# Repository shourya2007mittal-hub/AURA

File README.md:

# AURA

I made a custom Tailless twin motor RC Plane with custom Flight Controller (based on STM32). The Flight Controller  will have 2 IMU's and a barometer for precise data collection. The Plane design will include a tailless structure and the motions will be controlled by the flaps on the wings. I have also made custom ESc for the Plane as well.

## Features
- Base on  STM32F401CBUx 
- Has dual IMU (MPU_6050)(ICM-20948)
- Has a Barometer (BMP280)
- Uses 2 Light-Weight Servoes
- Uses Custom flight-controller
- Tailless twin motor Design
- Custom ESC for plane 

# ✈️ RC Plane Bill of Materials (BOM)

This repository contains the complete **Bill of Materials (BOM)** for the RC Plane project, including component quantities, unit prices, total costs, and supplier links.

## 📦 Bill of Materials

| Item | Quantity | Unit Price (USD) | Total Price (USD) | Source |
|------|:--------:|-----------------:|------------------:|--------|
| PCB + PCBA (Flight Controller + ESC) | 1 | $253.46 | $253.46 | https://jlcpcb.com |
| PCB Shipping + coupons | 1 | $17.32 | $17.32 | https://jlcpcb.com |
| Brushless Motor | 2 | $15.20 | $30.40 | https://robu.in/product/r2207-2207-2450kv-ccw-fpv-brushless-motor/ |
| Receiver / Transmitter | 1 | $0 | $0 Funded by me |https://robocraze.com/products/fly-sky-fs-i6x-2-4ghz-6ch-afhds-2a-rc-transmitter-with-fs-ia10b-2-4ghz-10ch-receiver?_pos=6&_sid=c7af4b55f&_ss=r |
| 12V Battery | 1 | $5.78 | $5.78 | https://robocraze.com/products/11-1v-2200mah-li-ion-battery?_pos=18&_sid=25292ddd5&_ss=r |
| SG90 Servo | 2 | $0.96 | $1.92 | https://robocraze.com/products/sg90-micro-servo-motor?_pos=1&_sid=88e48e080&_ss=r |
| 3D Printed Plane | 1 | $41.86 | $41.86 |https://jlc3dp.com/ |

---

## 💰 Cost Summary

| Category | Amount (USD) |
|----------|-------------:|
| Total Component Cost | **$352.74** |

---

## 📋 Components Included

- PCB + PCBA
- PCB Shipping
- Brushless Motors (×2)
- Electronic Speed Controllers (ESCs) (×2)
- Receiver / Transmitter
- 12V Battery
- SG90 Micro Servos (×2)
- 3D Printed Aircraft Frame

### Schematic Flight Controller

###  PCB Design Flight Controller

### Schematic ESC

###  PCB Design ESC

### 3D Design

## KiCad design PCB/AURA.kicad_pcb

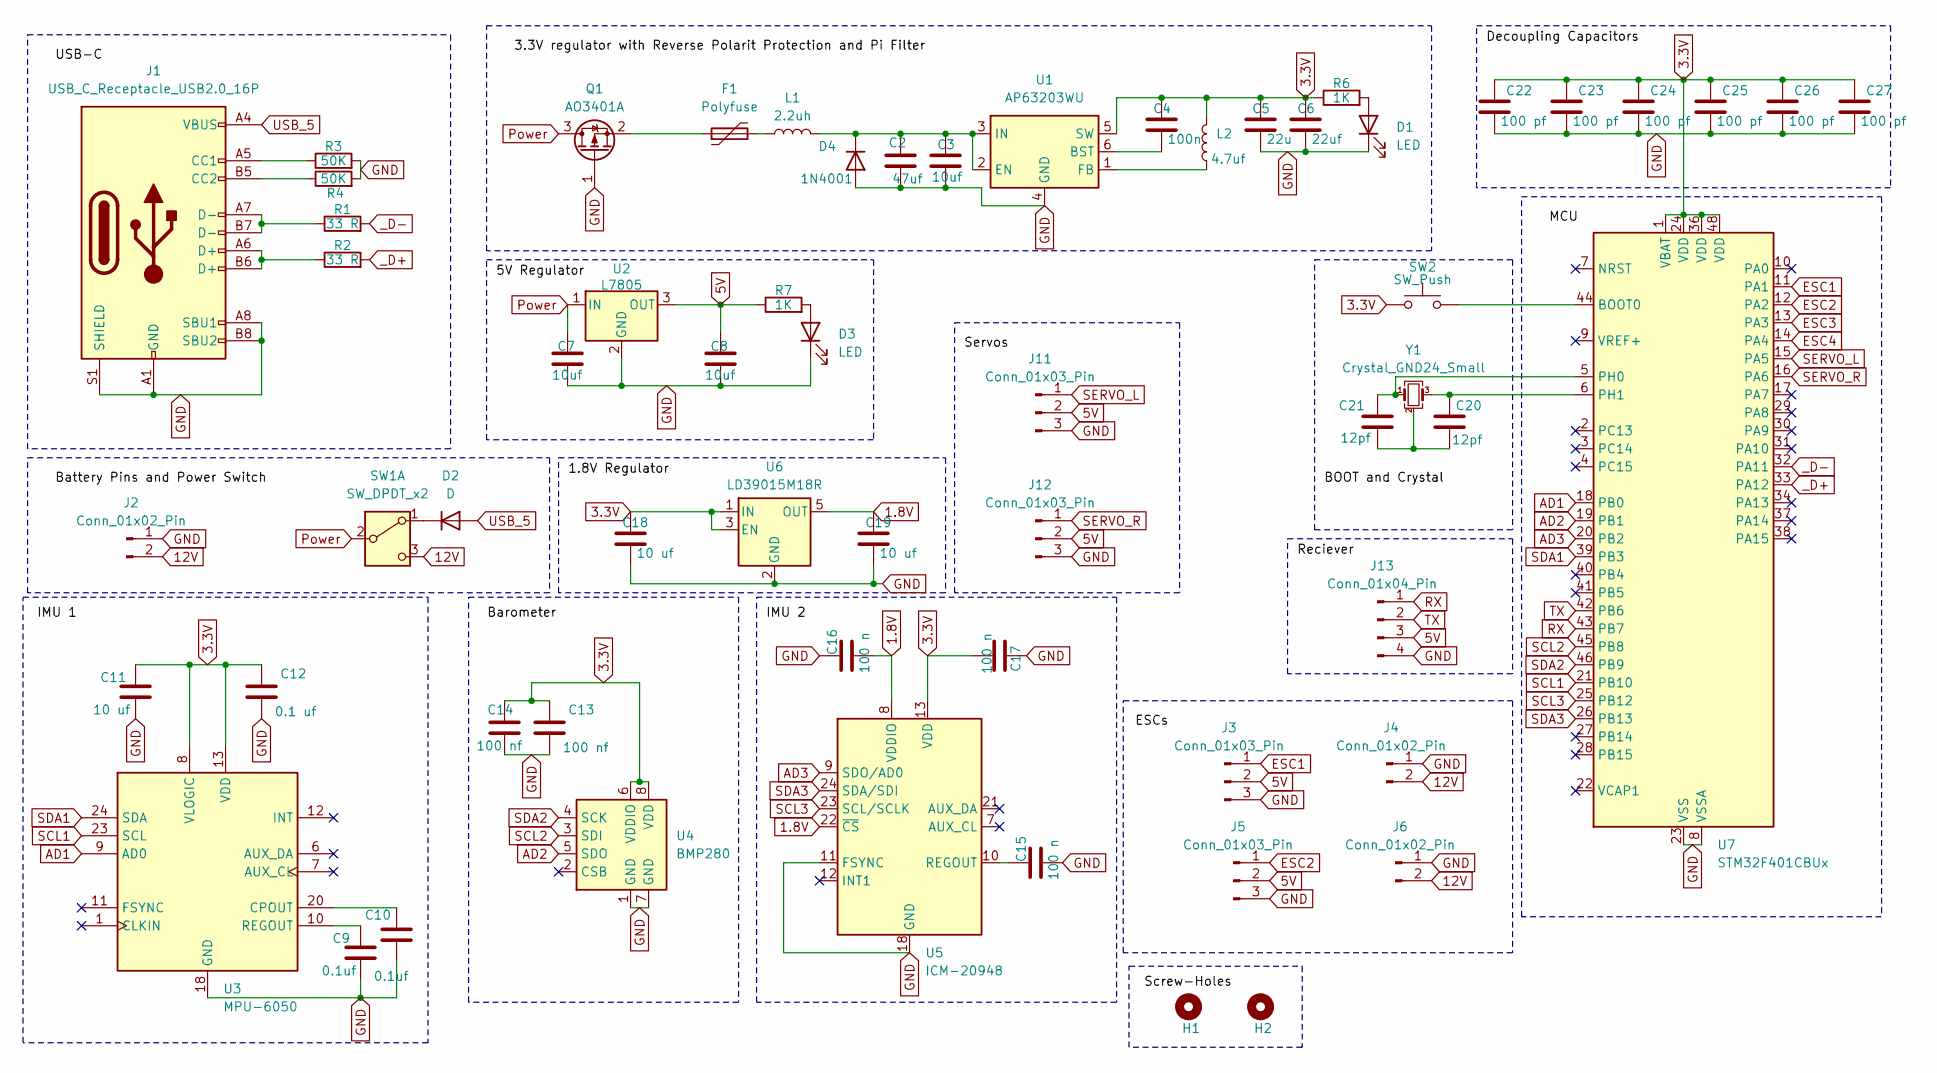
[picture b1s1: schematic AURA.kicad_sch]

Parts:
C2: 47uf; C_0201_0603Metric
C3, C7, C8: 10uf; C_0201_0603Metric
C4: 100n; C_0201_0603Metric
C5: 22u; C_0201_0603Metric
C6: 22uf; C_0201_0603Metric
C9, C10: 0.1uf; C_0201_0603Metric
C11, C18, C19: 10 uf; C_0201_0603Metric
C12: 0.1 uf; C_0201_0603Metric
C13, C14: 100 nf; C_0201_0603Metric
C15, C16, C17: 100 n; C_0201_0603Metric
C20, C21: 12pf; C_0201_0603Metric
C22, C23, C24, C25, C26, C27: 100 pf; C_0201_0603Metric
D1, D3: LED; LED_0201_0603Metric
D2: D; D_0201_0603Metric
D4: 1N4001; D_DO-41_SOD81_P5.08mm_Vertical_AnodeUp
F1: Polyfuse; C_0201_0603Metric
H1, H2: MountingHole; MountingHole_2.5mm_Pad
J1: USB_C_Receptacle_USB2.0_16P; USB_C_Receptacle_G-Switch_GT-USB-7010ASV
J2: Conn_01x02_Pin; AMASS_XT60-M_1x02_P7.20mm_Vertical
J3, J5, J11, J12: Conn_01x03_Pin; JST_EH_B3B-EH-A_1x03_P2.50mm_Vertical
J4, J6: Conn_01x02_Pin; AMASS_XT60-F_1x02_P7.20mm_Vertical
J13: Conn_01x04_Pin; JST_EH_B4B-EH-A_1x04_P2.50mm_Vertical
L1: 2.2uh; L_0603_1608Metric
L2: 4.7uf; L_0603_1608Metric
Q1: AO3401A; SOT-23
R1, R2: 33 R; R_0201_0603Metric_Pad0.64x0.40mm_HandSolder
R3, R4: 50K; R_0201_0603Metric_Pad0.64x0.40mm_HandSolder
R6, R7: 1K; R_0201_0603Metric_Pad0.64x0.40mm_HandSolder
SW1: SW_DPDT_x2; SW_PUSH_E-Switch_FS5700DP_DPDT
SW2: SW_Push; SW_Tactile_Straight_KSA0Axx1LFTR
U1: AP63203WU; TSOT-23-6
U2: L7805; TO-252-2
U3: MPU-6050; InvenSense_QFN-24_4x4mm_P0.5mm
U4: BMP280; Bosch_LGA-8_2x2.5mm_P0.65mm_ClockwisePinNumbering
U5: ICM-20948; InvenSense_QFN-24_3x3mm_P0.4mm
U6: LD39015M18R; SOT-23-5
U7: STM32F401CBUx; QFN-48-1EP_7x7mm_P0.5mm_EP5.6x5.6mm
Y1: Crystal_GND24_Small; Crystal_SMD_0603-4Pin_6.0x3.5mm

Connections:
1.8V: C16.2, C19.1, U5.8 (VDDIO), U5.22 (~CS), U6.5 (OUT)
3.3V: C4.1, C5.1, C6.1, C11.1, C12.1, C13.1, C14.1, C17.2, C18.1, C22.1, C23.1, C24.1, C25.1, C26.1, C27.1, L2.2, R6.1, SW2.1, U1.5 (SW), U3.8 (VLOGIC), U3.13 (VDD), U4.6 (VDDIO), U4.8 (VDD), U5.13 (VDD), U6.1 (IN), U6.3 (EN), U7.1 (VBAT), U7.24 (VDD), U7.36 (VDD), U7.48 (VDD)
5V: C8.1, J3.2, J5.2, J11.2, J12.2, J13.3, R7.1, U2.3 (OUT)
12V: J2.2, J4.2, J6.2, SW1.3 (C)
AD1: U3.9 (AD0), U7.18 (PB0)
AD2: U4.5 (SDO), U7.19 (PB1)
AD3: U5.9 (SDO/AD0), U7.20 (PB2)
ESC1: J3.1, U7.11 (PA1)
ESC2: J5.1, U7.12 (PA2)
ESC3: U7.13 (PA3)
ESC4: U7.14 (PA4)
GND: C2.2, C3.2, C5.2, C6.2, C7.2, C8.2, C9.2, C10.2, C11.2, C12.2, C13.2, C14.2, C15.2, C16.1, C17.1, C18.2, C19.2, C22.2, C23.2, C24.2, C25.2, C26.2, C27.2, D1.1 (K), D3.1 (K), D4.2 (A), J1.A1 (GND), J1.A8 (SBU1), J1.A12 (GND), J1.B1 (GND), J1.B8 (SBU2), J1.B12 (GND), J1.S1 (SHIELD), J2.1, J3.3, J4.1, J5.3, J6.1, J11.3, J12.3, J13.4, Q1.1 (G), R3.2, R4.2, U1.4 (GND), U2.2 (GND), U3.18 (GND), U4.1 (GND), U4.7 (GND), U5.11 (FSYNC), U5.18 (GND), U5.20 (GND), U6.2 (GND), U7.8 (VSSA), U7.23 (VSS), U7.35 (VSS), U7.47 (VSS), U7.49 (VSS)
unnamed: C20.2, C21.2, Y1.2 (G), Y1.4 (G)
unnamed: D1.2 (A), R6.2
unnamed: D2.1 (K), SW1.1 (A)
unnamed: D3.2 (A), R7.2
unnamed: C2.1, C3.1, D4.1 (K), L1.2, U1.2 (EN), U1.3 (IN)
unnamed: F1.2, L1.1
unnamed: J1.A5 (CC1), R3.1
unnamed: J1.B5 (CC2), R4.1
unnamed: J1.A6 (D+), J1.B6 (D+), R2.1
unnamed: J1.A7 (D-), J1.B7 (D-), R1.1
unnamed: F1.1, Q1.2 (S)
unnamed: C4.2, U1.6 (BST)
unnamed: L2.1, U1.1 (FB)
unnamed: C10.1, U3.20 (CPOUT)
unnamed: C9.1, U3.10 (REGOUT)
unnamed: C15.1, U5.10 (REGOUT)
unnamed: SW2.2, U7.44 (BOOT0)
unnamed: C21.1, U7.5 (PH0), Y1.1
unnamed: C20.1, U7.6 (PH1), Y1.3
Power: C7.1, Q1.3 (D), SW1.2 (B), U2.1 (IN)
RX: J13.1, U7.43 (PB7)
SCL1: U3.23 (SCL), U7.21 (PB10)
SCL2: U4.3 (SDI), U7.45 (PB8)
SCL3: U5.23 (SCL/SCLK), U7.25 (PB12)
SDA1: U3.24 (SDA), U7.39 (PB3)
SDA2: U4.4 (SCK), U7.46 (PB9)
SDA3: U5.24 (SDA/SDI), U7.26 (PB13)
SERVO_L: J11.1, U7.15 (PA5)
SERVO_R: J12.1, U7.16 (PA6)
TX: J13.2, U7.42 (PB6)
USB_5: D2.2 (A), J1.A4 (VBUS), J1.A9 (VBUS), J1.B4 (VBUS), J1.B9 (VBUS)
_D+: R2.2, U7.33 (PA12)
_D-: R1.2, U7.32 (PA11)

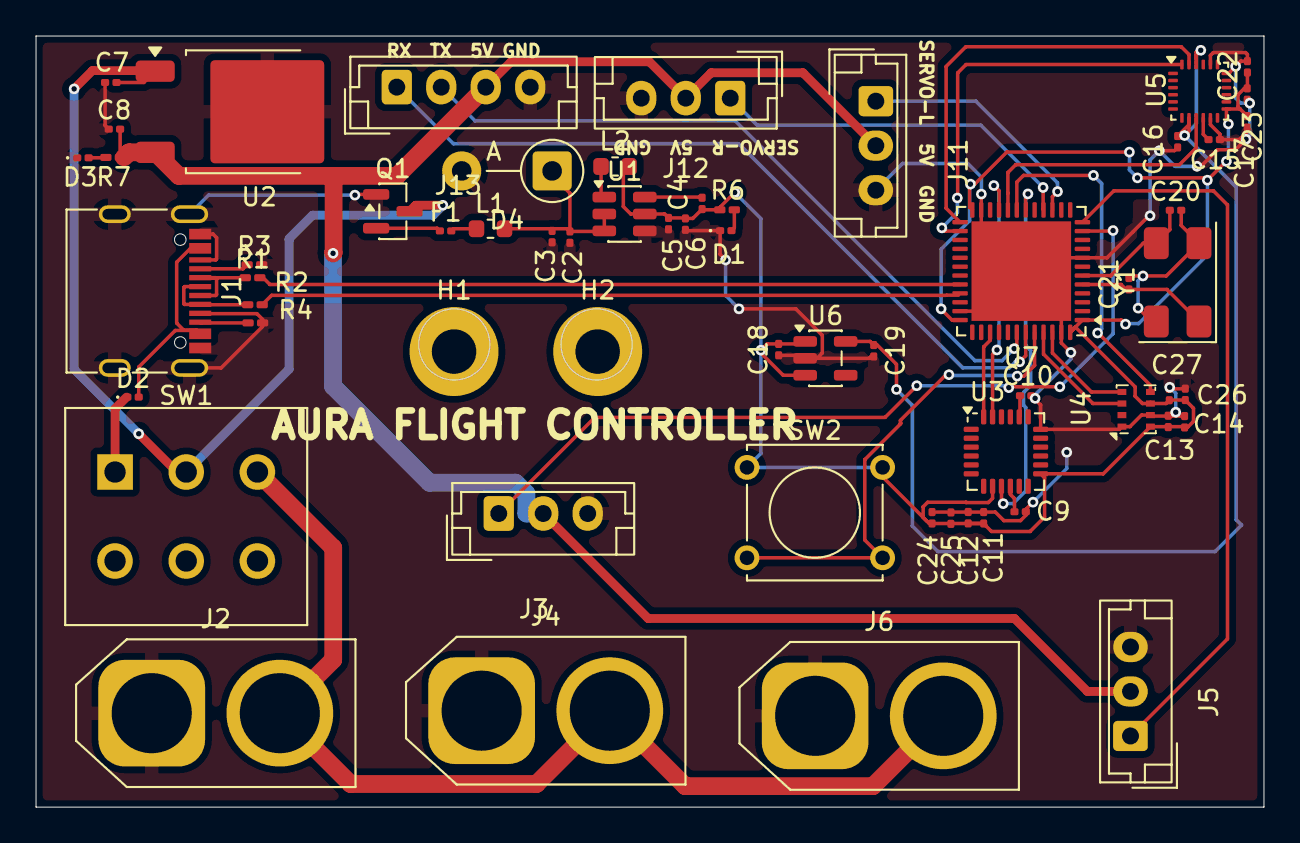
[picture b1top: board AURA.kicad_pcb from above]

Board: 2 copper layers, 69.0 x 43.3 mm, 61 parts (0 on the bottom side), 43 nets.

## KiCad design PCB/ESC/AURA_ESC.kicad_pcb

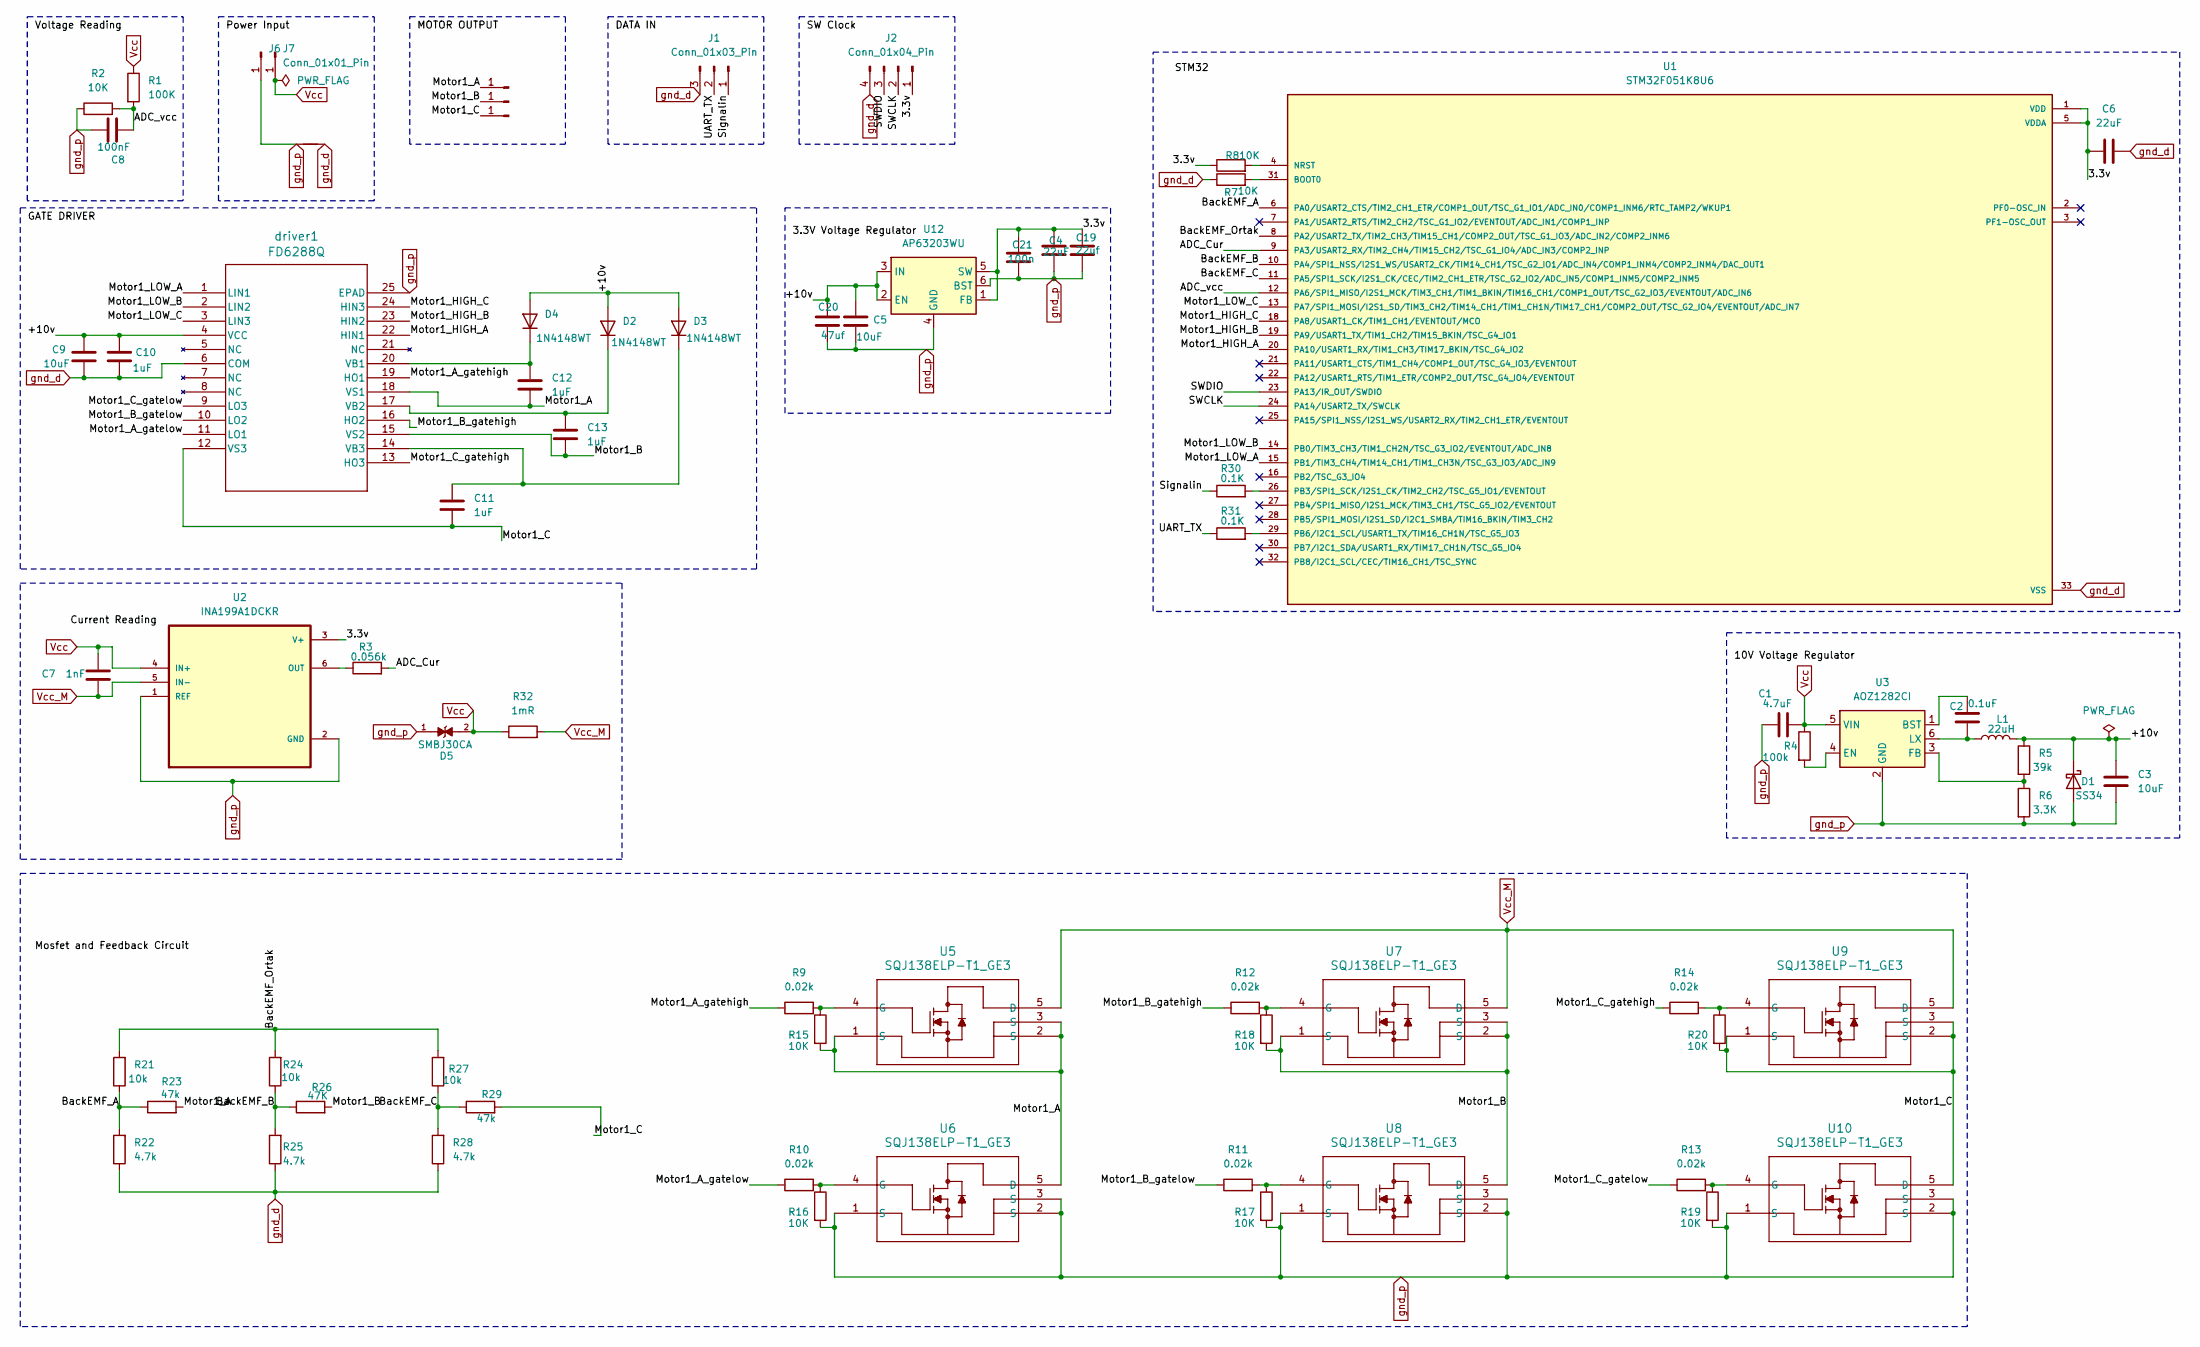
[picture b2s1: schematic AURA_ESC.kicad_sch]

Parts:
C1: 4.7uF; C_0805_2012Metric
C2: 0.1uF; C_0603_1608Metric
C3, C5, C9: 10uF; C_1206_3216Metric
C4, C6: 22uF; C_1206_3216Metric
C7: 1nF; C_0603_1608Metric
C8: 100nF; C_0603_1608Metric
C10, C11, C12, C13: 1uF; C_0805_2012Metric
C19: 22uf; C_0201_0603Metric
C20: 47uf; C_0201_0603Metric
C21: 100n; C_0201_0603Metric
D1: SS34; D_SMA
D2, D3, D4: 1N4148WT; D_SOD-523
D5: SMBJ30CA; DIOM4336X265N; PARTREV I2102
J1: Conn_01x03_Pin; PinHeader_1x03_P2.54mm_Vertical
J2: Conn_01x04_Pin; PinHeader_1x04_P2.54mm_Vertical
J3, J4, J5, J6, J7: Conn_01x01_Pin; PinHeader_1x01_P2.54mm_Vertical
L1: 22uH; L_6.3x6.3_H3
NT1: NetTie_2; NetTie-2_SMD_Pad0.5mm
R1: 100K; R_0603_1608Metric
R2, R7, R8, R15, R16, R17, R18, R19, R20: 10K; R_0603_1608Metric
R3: 0.056k; R_0603_1608Metric
R4: 100k; R_0603_1608Metric
R5: 39k; R_0603_1608Metric
R6: 3.3K; R_0603_1608Metric
R9, R10, R11, R12, R13, R14: 0.02k; R_0603_1608Metric
R21, R24, R27: 10k; R_0603_1608Metric
R22, R25, R28: 4.7k; R_0603_1608Metric
R23, R29: 47k; R_0603_1608Metric
R26: 47K; R_0603_1608Metric
R30, R31: 0.1K; R_0603_1608Metric
R32: 1mR; R_2512_6332Metric
U1: STM32F051K8U6; QFN50P500X500X60-33N; PARTREV 7
U2: INA199A1DCKR; SOT65P210X110-6N
U3: AOZ1282CI; SOT-23-6
U5, U6, U7, U8, U9, U10: SQJ138ELP-T1_GE3; PowerPAK_SO-8L_3_VIS
U12: AP63203WU; TSOT-23-6
driver1: FD6288Q; QFN24_FOR-M

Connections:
/+10v: C3.1, C5.1, C9.1, C10.1, C20.1, D1.1 (K), D2.2 (A), D3.2 (A), D4.2 (A), L1.2, R5.1, U12.2 (EN), U12.3 (IN), driver1.4 (VCC)
/ADC_Cur: R3.2, U1.9 (PA3/USART2_RX/TIM2_CH4/TIM15_CH2/TSC_G1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)
/ADC_vcc: C8.2, R1.2, R2.2, U1.12 (PA6/SPI1_MISO/I2S1_MCK/TIM3_CH1/TIM1_BK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)
/BackEMF_A: R21.1, R22.2, R23.1, U1.6 (PA0/USART2_CTS/TIM2_CH1_ETR/COMP1_OUT/T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)
/BackEMF_B: R24.1, R25.2, R26.1, U1.10 (PA4/SPI1_NSS/I2S1_WS/USART2_CK/TIM14_CH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)
/BackEMF_C: R27.1, R28.2, R29.1, U1.11 (PA5/SPI1_SCK/I2S1_CK/CEC/TIM2_CH1_ETR/T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)
/BackEMF_Ortak: R21.2, R24.2, R27.2, U1.8 (PA2/USART2_TX/TIM2_CH3/TIM15_CH1/COMP2_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)
/Motor1_A: C12.2, J3.1 (Pin_1_1), R15.2, R23.2, U5.1 (S), U5.2 (S), U5.3 (S), U6.5 (D), driver1.18 (VS1)
/Motor1_A_gatehigh: R9.1, driver1.19 (HO1)
/Motor1_A_gatelow: R10.1, driver1.11 (LO1)
/Motor1_B: C13.2, J4.1 (Pin_1_1), R18.2, R26.2, U7.1 (S), U7.2 (S), U7.3 (S), U8.5 (D), driver1.15 (VS2)
/Motor1_B_gatehigh: R12.1, driver1.16 (HO2)
/Motor1_B_gatelow: R11.1, driver1.10 (LO2)
/Motor1_C: C11.2, J5.1 (Pin_1_1), R20.2, R29.2, U9.1 (S), U9.2 (S), U9.3 (S), U10.5 (D), driver1.12 (VS3)
/Motor1_C_gatehigh: R14.1, driver1.13 (HO3)
/Motor1_C_gatelow: R13.1, driver1.9 (LO3)
/Motor1_HIGH_A: U1.20 (PA10/USART1_RX/TIM1_CH3/TIM17_BKIN/TSC_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), driver1.22 (HIN1)
/Motor1_HIGH_B: U1.19 (PA9/USART1_TX/TIM1_CH2/TIM15_BKIN/TSC_G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), driver1.23 (HIN2)
/Motor1_HIGH_C: U1.18 (PA8/USART1_CK/TIM1_CH1/EVENTOUT/MCO), driver1.24 (HIN3)
/Motor1_LOW_A: U1.15 (PB1/TIM3_CH4/TIM14_CH1/TIM1_CH3N/TSC_G3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), driver1.1 (LIN1)
/Motor1_LOW_B: U1.14 (PB0/TIM3_CH3/TIM1_CH2N/TSC_G3_IO2/EVENT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), driver1.2 (LIN2)
/Motor1_LOW_C: U1.13 (PA7/SPI1_MOSI/I2S1_SD/TIM3_CH2/TIM14_CH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), driver1.3 (LIN3)
/SWCLK: J2.2, U1.24 (PA14/USART2_TX/SWCLK)
/SWDIO: J2.3, U1.23 (PA13/IR_OUT/SWDIO)
/Signalin: J1.1, R30.1
/UART_TX: J1.2, R31.1
unnamed: C13.1, D2.1 (K), driver1.17 (VB2)
unnamed: C11.1, D3.1 (K), driver1.14 (VB3)
unnamed: C12.1, D4.1 (K), driver1.20 (VB1)
unnamed: R7.2, U1.31 (BOOT0)
unnamed: R8.2, U1.4 (NRST)
unnamed: R30.2, U1.26 (PB3/SPI1_SCK/I2S1_CK/TIM2_CH2/TSC_G5_IO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)
unnamed: R31.2, U1.29 (PB6/I2C1_SCL/USART1_TX/TIM16_CH1N/TSC_G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)
unnamed: R3.1, U2.6 (OUT)
unnamed: C2.1, U3.1 (BST)
unnamed: R4.2, U3.4 (EN)
unnamed: R5.2, R6.1, U3.3 (FB)
unnamed: C2.2, L1.1, U3.6 (LX)
unnamed: R9.2, R15.1, U5.4 (G)
unnamed: R10.2, R16.1, U6.4 (G)
unnamed: R12.2, R18.1, U7.4 (G)
unnamed: R11.2, R17.1, U8.4 (G)
unnamed: R14.2, R20.1, U9.4 (G)
unnamed: R13.2, R19.1, U10.4 (G)
VDD: C4.1, C6.2, C19.1, C21.1, J2.1, R8.1, U1.1 (VDD), U1.5 (VDDA), U1.17 (VDD), U2.3 (V+), U12.1 (FB), U12.5 (SW)
Vcc: C1.1, C7.2, D5.2, J7.1 (Pin_1_1), R1.1, R4.1, R32.1, U2.4 (IN+), U3.5 (VIN)
Vcc_M: C7.1, R32.2, U2.5 (IN-), U5.5 (D), U7.5 (D), U9.5 (D)
gnd_d: C6.1, C9.2, C10.2, J1.3, J2.4, NT1.2, R7.1, R22.1, R25.1, R28.1, U1.33 (VSS), driver1.6 (COM)
gnd_p: C1.2, C3.2, C4.2, C5.2, C8.1, C19.2, C20.2, C21.2, D1.2 (A), D5.1, J6.1 (Pin_1_1), NT1.1, R2.1, R6.2, R16.2, R17.2, R19.2, U2.1 (REF), U2.2 (GND), U3.2 (GND), U6.1 (S), U6.2 (S), U6.3 (S), U8.1 (S), U8.2 (S), U8.3 (S), U10.1 (S), U10.2 (S), U10.3 (S), U12.4 (GND), U12.6 (BST), driver1.25 (EPAD)

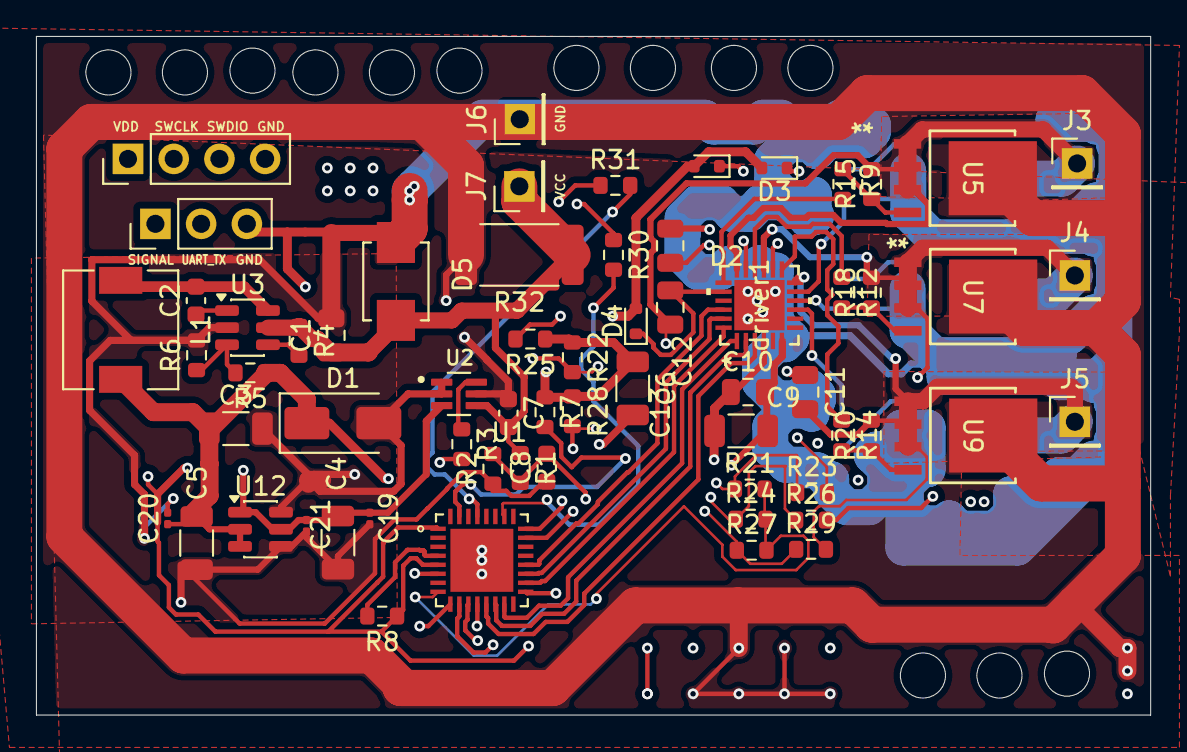
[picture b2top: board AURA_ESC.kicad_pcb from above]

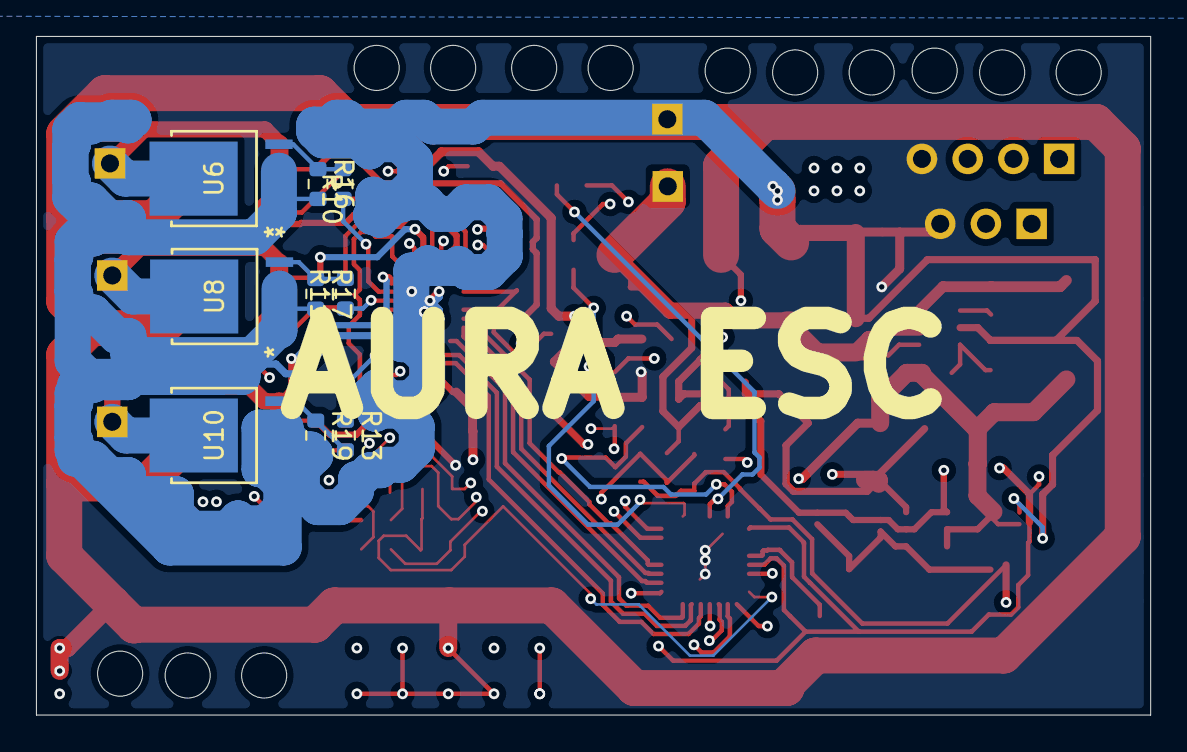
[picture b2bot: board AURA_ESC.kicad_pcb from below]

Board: 4 copper layers, 61.9 x 37.7 mm, 73 parts (9 on the bottom side), 49 nets.

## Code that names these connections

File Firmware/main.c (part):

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#define SBUS_FRAME_SIZE 25

// --- PERIPHERAL HANDLES ---
I2C_HandleTypeDef hi2c1;   // IMU 1 (MPU6050) via PB6/PB7
I2C_HandleTypeDef hi2c2;   // Barometer (BMP280) via PB10/PB3
TIM_HandleTypeDef htim1;   // ESCs (PA8, PA9)
TIM_HandleTypeDef htim2;   // Servos (PA0, PA1)
UART_HandleTypeDef huart1; // SBUS Receiver Input (PA10)

// --- FLIGHT CONTROL VARIABLES ---
float roll_input = 0.0f, pitch_input = 0.0f, throttle_input = 1000.0f;
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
